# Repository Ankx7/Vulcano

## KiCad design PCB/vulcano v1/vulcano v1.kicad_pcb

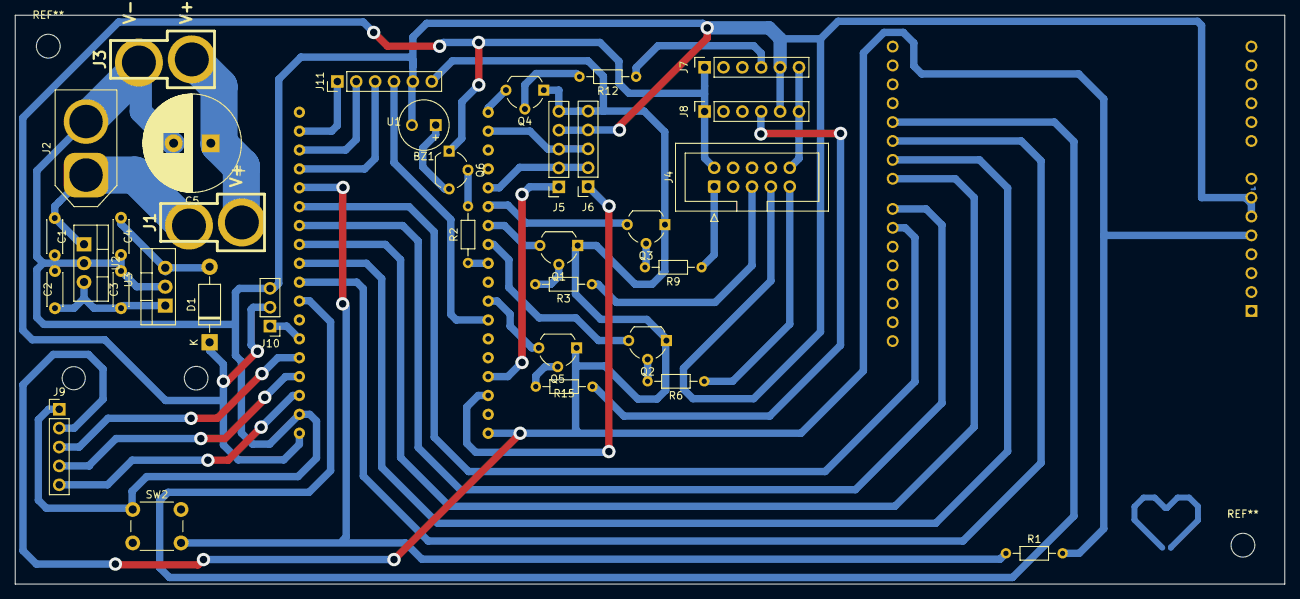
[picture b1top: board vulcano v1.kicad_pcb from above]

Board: 2 copper layers, 170.8 x 76.5 mm, 36 parts (1 on the bottom side), 45 nets.

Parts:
A1: Arduino_UNO_R2
BZ1: Buzzer; MagneticBuzzer_Kingstate_KCG0601
C1, C3: 0.33uF; C_Disc_D4.3mm_W1.9mm_P5.00mm
C2, C4: 0.1uF; C_Disc_D4.3mm_W1.9mm_P5.00mm
C5: C_Polarized_US; CP_Radial_D13.0mm_P5.00mm
D1: 1N4007; D_DO-41_SOD81_P10.16mm_Horizontal
J1, J3: Screw_Terminal_01x02; DEANS
J2: Screw_Terminal_01x02; AMASS_XT60-M_1x02_P7.20mm_Vertical
J4: Conn_02x05_Counter_Clockwise; IDC-Header_2x05_P2.54mm_Vertical
J5, J6: Conn_01x05_Pin; PinSocket_1x05_P2.54mm_Vertical
J7, J8: Conn_01x06_Pin; PinSocket_1x06_P2.54mm_Vertical
J9: Conn_01x05_Pin; PinHeader_1x05_P2.54mm_Vertical
J10: Conn_01x03_Pin; PinHeader_1x03_P2.54mm_Vertical
J11: Conn_01x06_Pin; PinHeader_1x06_P2.54mm_Vertical
Q1, Q2, Q3, Q4, Q5, Q6: BC547; TO-92_Wide
R1, R2, R3, R6, R9, R12, R15: 4k7; R_Axial_DIN0204_L3.6mm_D1.6mm_P7.62mm_Horizontal
SW2: SW_Push; SW_PUSH_6mm
U1: DOIT-ESP32-DEVKIT-V1; ESP32-DOIT-DEVKIT
U2: LM7809_TO220; TO-220-3_Vertical
U3: LM7806_TO220; TO-220-3_Vertical

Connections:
38KHZ: J4.10, J7.6, J8.6
+3.3V: A1.5 (+5V), J5.5, J6.5, J9.2, J11.6, Q1.1 (C), Q2.1 (C), Q3.1 (C), Q4.1 (C), Q5.1 (C), R1.2, U1.19 (3V3)
+5V: D1.1 (K), J4.2, J7.1, J8.1, J10.2, Q6.1 (C), U1.18 (VIN)
+6V: C4.1, D1.2 (A), U3.3 (VO)
+9V: C2.1, C3.1, U2.3 (VO), U3.1 (VI)
+12V: C1.1, J1.2, J2.1, U2.1 (VI)
AIN1: A1.22 (D7), U1.8 (GPIO25_ADC2-CH8_DAC1_RTC-GPIO6)
AIN2: A1.23 (D8), U1.7 (GPIO33_ADC1-CH5_RTC-GPIO8)
BIN1: A1.19 (D4), U1.11 (GPIO14_ADC2-CH6_HSPI-CLK_RTC-GPIO16)
BIN2: A1.24 (D9), U1.6 (GPIO32_ADC1-CH4_RTC-GPIO9)
CLK: J9.5, U1.16 (GPIO11_CSC/CMD)
CNY_1: J11.1, U1.2 (GPIO36_ADC-CH0_SENS-VP_RTC-GPIO0)
CNY_2: J11.2, U1.3 (GPIO39_ADC1-CH3_SENS-VN_RTC-GPIO3)
CNY_3: J11.3, U1.4 (GPIO34_ADC1-CH6_RTC-GPIO4)
CNY_4: J11.4, U1.25 (GPIO2_ADC2-CH2_RTC-GPIO12)
DI: J10.1, U1.13 (GPIO13_ADC2-CH4_HSPI-MOSI_RTC-GPIO14)
DT: J9.4, U1.15 (GPIO10_SWP/SD3)
GND: A1.6 (GND), A1.7 (GND), BZ1.2 (+), C1.2, C2.2, C3.2, C4.2, C5.2, J2.2, J3.2, J4.7, J5.4, J6.4, J7.5, J8.5, J9.1, J10.3, J11.5, SW2.1, U1.17 (GND), U2.2 (GND), U3.2 (GND)
INIT: R1.1, SW2.2, U1.5 (GPIO35_ADC1-CH7_RTC-GPIO5)
unnamed: BZ1.1 (-), Q6.3 (E)
unnamed: Q1.2 (B), R3.2
unnamed: Q2.2 (B), R6.2
unnamed: Q3.2 (B), R9.2
unnamed: Q4.2 (B), R12.2
unnamed: Q5.2 (B), R15.2
unnamed: Q6.2 (B), R2.2
PWMA: A1.20 (D5), U1.10 (GPIO27_ADC2-CH7_RTC-GPIO17)
PWMB: A1.21 (D6), U1.9 (GPIO26_ADC2-CH9_DAC2_RTC-GPIO7)
RX: J7.4, R12.1
RX_1: J8.4, R15.1
SCL: J5.3, J6.3, U1.35 (GPIO22_I2C-SCL)
SDA: J5.2, J6.2, U1.32 (GPIO21_I2C-SDA)
SENSOR_1_PIN: Q1.3 (E), U1.30 (GPIO18_VSPI-CLK)
SENSOR_2_PIN: Q2.3 (E), U1.29 (GPIO5_VSPI-CS0)
SENSOR_3_PIN: Q3.3 (E), U1.31 (GPIO19_VSPI-MISO)
SENSOR_4_PIN: Q4.3 (E), U1.36 (GPIO23_VSPI-MOSI)
SENSOR_5_PIN: Q5.3 (E), U1.26 (GPIO4_ADC2-CH0_RTC-GPIO10)
SW: J9.3, U1.14 (GPIO9_SHD/SD2)
Sensores: J4.5, R3.1
Sensores_2: J4.9, R6.1
Sensores_3: J4.1, R9.1
VCC: C5.1, J1.1, J3.1
X_SHUT_1: J6.1, U1.21 (GPIO7_SDO/SD0)
X_SHUT_2: J5.1, U1.22 (GPIO8_SDI/SD1)
buzzer: R2.1, U1.28 (GPIO17_UART2-TX)

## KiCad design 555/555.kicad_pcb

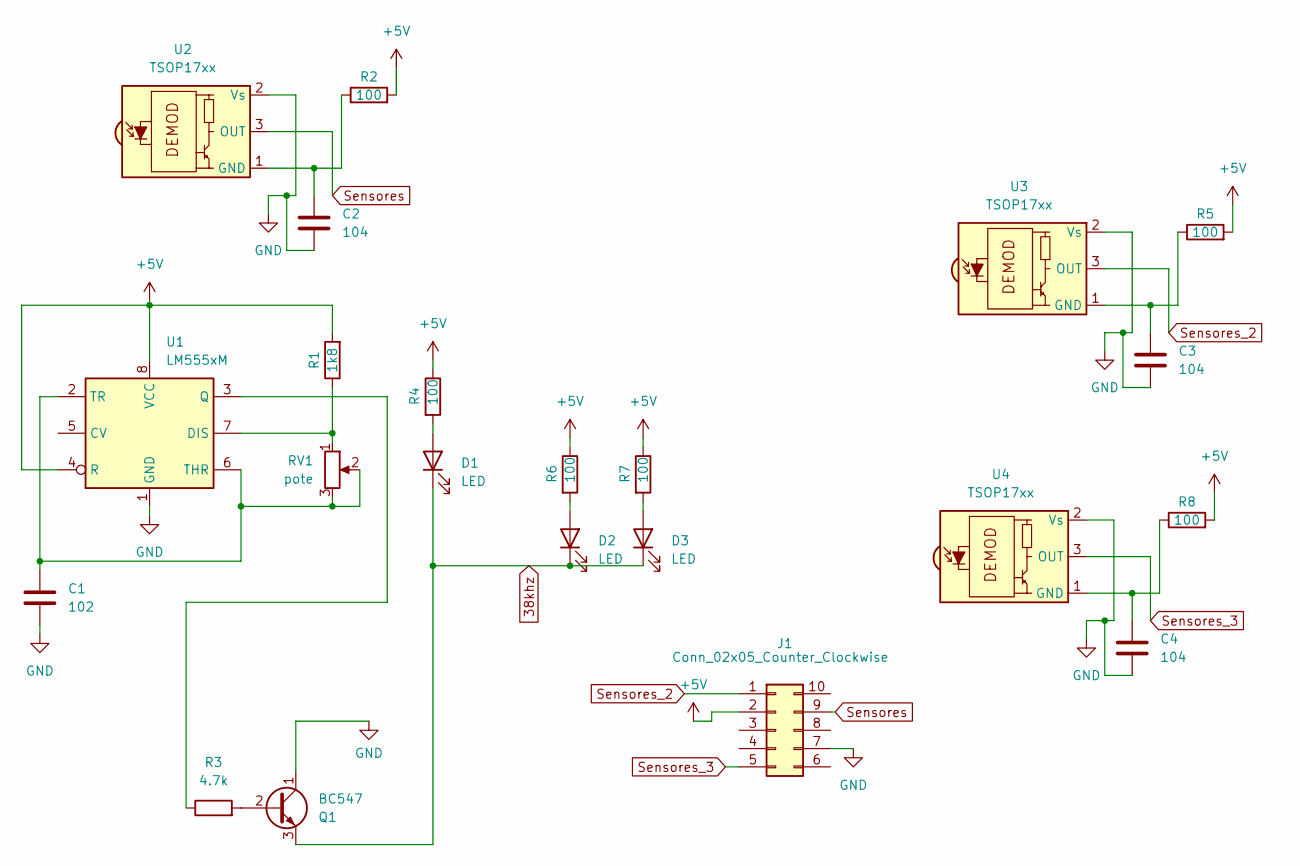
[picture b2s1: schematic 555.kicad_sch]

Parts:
C1: 102; C_Disc_D4.3mm_W1.9mm_P5.00mm
C2, C3, C4: 104; C_Disc_D4.3mm_W1.9mm_P5.00mm
D1, D2, D3: LED; LED_D5.0mm_Horizontal_O1.27mm_Z3.0mm
J1: Conn_02x05_Counter_Clockwise; IDC-Header_2x05_P2.54mm_Horizontal
Q1: BC547; TO-92_Wide
R1: 1k8; R_1206_3216Metric_Pad1.30x1.75mm_HandSolder
R2, R4, R5, R8: 100; R_1206_3216Metric_Pad1.30x1.75mm_HandSolder
R3: 4.7k; R_1206_3216Metric_Pad1.30x1.75mm_HandSolder
R6, R7: 100; R_Axial_DIN0207_L6.3mm_D2.5mm_P10.16mm_Horizontal
RV1: pote; Potentiometer_Bourns_3296W_Vertical
U1: LM555xM; DIP-8_W7.62mm
U2, U3, U4: TSOP17xx; TO-92S_Wide

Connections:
38khz: D1.1 (K), D2.1 (K), D3.1 (K), Q1.3 (E)
+5V: J1.2, R1.2, R2.2, R4.1, R5.2, R6.1, R7.1, R8.2, U1.4 (R), U1.8 (VCC)
GND: C1.2, C2.2, C3.2, C4.2, J1.7, Q1.1 (C), U1.1 (GND), U2.2 (Vs), U3.2 (Vs), U4.2 (Vs)
unnamed: D1.2 (A), R4.2
unnamed: D2.2 (A), R6.2
unnamed: D3.2 (A), R7.2
unnamed: Q1.2 (B), R3.2
unnamed: R1.1, RV1.1, U1.7 (DIS)
unnamed: R3.1, U1.3 (Q)
unnamed: C1.1, RV1.2, RV1.3, U1.2 (TR), U1.6 (THR)
unnamed: C2.1, R2.1, U2.1 (GND)
unnamed: C3.1, R5.1, U3.1 (GND)
unnamed: C4.1, R8.1, U4.1 (GND)
Sensores: J1.9, U2.3 (OUT)
Sensores_2: J1.1, U3.3 (OUT)
Sensores_3: J1.5, U4.3 (OUT)

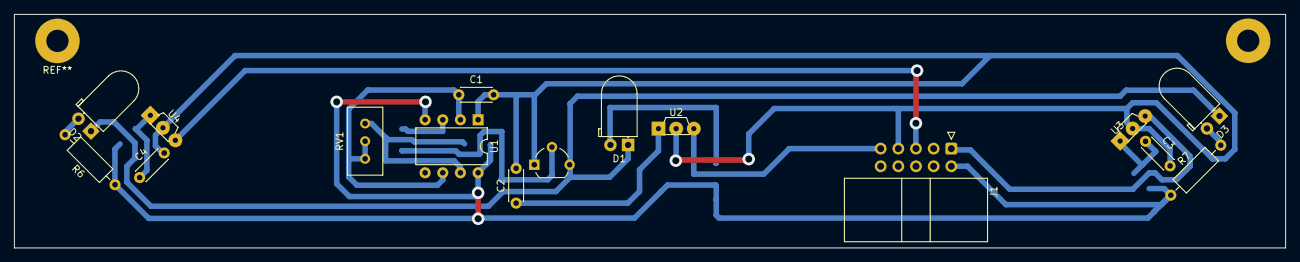
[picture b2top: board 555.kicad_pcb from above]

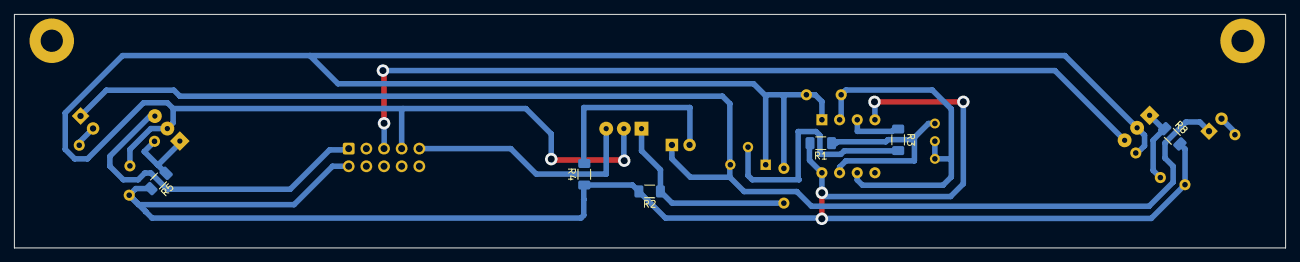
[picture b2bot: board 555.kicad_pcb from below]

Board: 2 copper layers, 182.8 x 33.6 mm, 22 parts (6 on the bottom side), 16 nets.

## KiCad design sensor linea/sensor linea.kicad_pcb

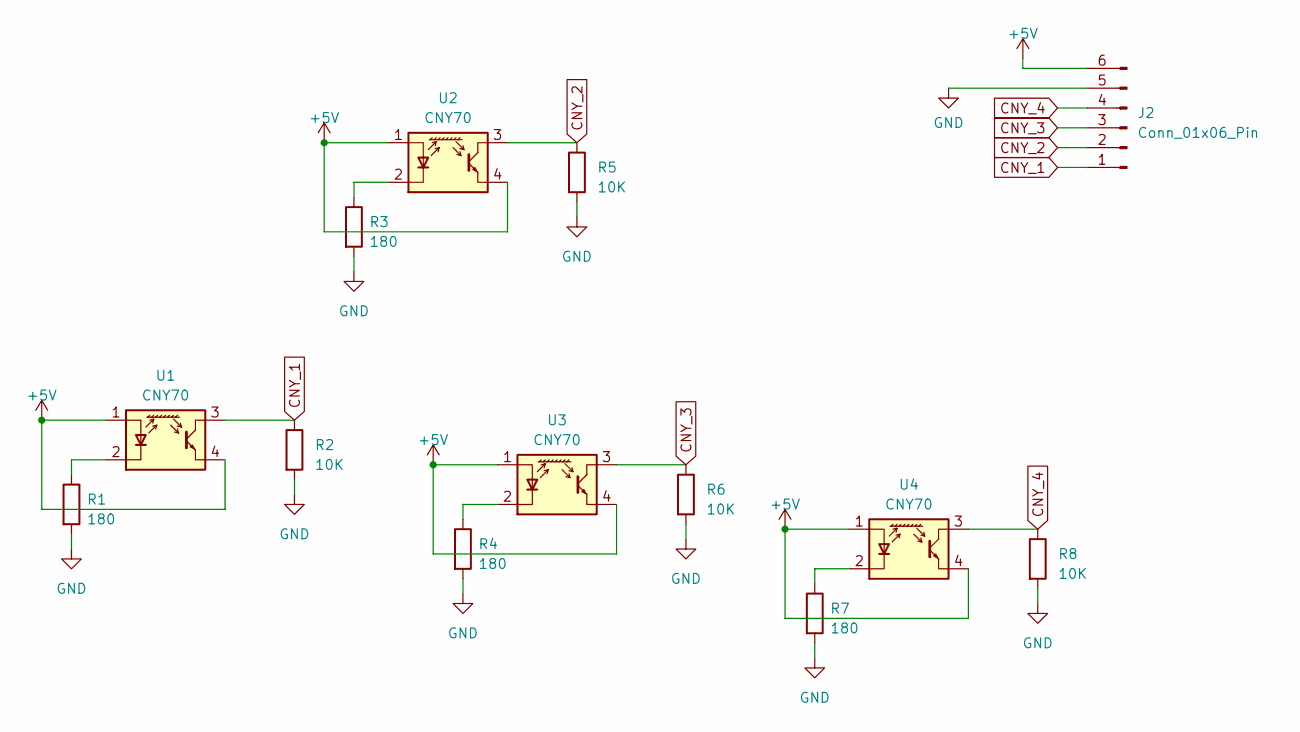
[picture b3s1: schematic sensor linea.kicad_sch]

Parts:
J2: Conn_01x06_Pin; PinHeader_1x06_P2.54mm_Horizontal
R1, R3, R4, R7: 180; R_1206_3216Metric_Pad1.30x1.75mm_HandSolder
R2, R5, R6, R8: 10K; R_1206_3216Metric_Pad1.30x1.75mm_HandSolder
U1, U2, U3, U4: CNY70; Vishay_CNY70

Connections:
+5V: J2.6, U1.1 (A), U1.4 (E), U2.1 (A), U2.4 (E), U3.1 (A), U3.4 (E), U4.1 (A), U4.4 (E)
CNY_1: J2.1, R2.1, U1.3 (C)
CNY_2: J2.2, R5.1, U2.3 (C)
CNY_3: J2.3, R6.1, U3.3 (C)
CNY_4: J2.4, R8.1, U4.3 (C)
GND: J2.5, R1.2, R2.2, R3.2, R4.2, R5.2, R6.2, R7.2, R8.2
unnamed: R1.1, U1.2 (K)
unnamed: R3.1, U2.2 (K)
unnamed: R4.1, U3.2 (K)
unnamed: R7.1, U4.2 (K)

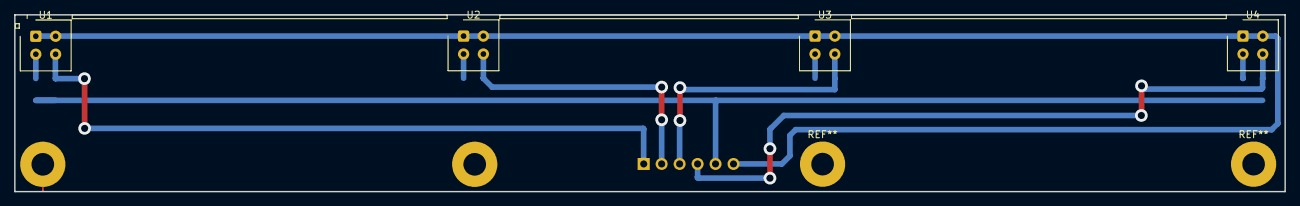
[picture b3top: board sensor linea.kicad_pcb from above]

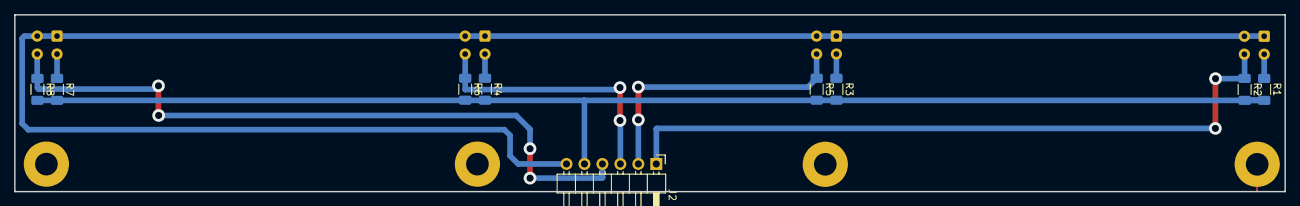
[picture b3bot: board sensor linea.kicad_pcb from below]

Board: 2 copper layers, 179.7 x 25.0 mm, 13 parts (9 on the bottom side), 10 nets.

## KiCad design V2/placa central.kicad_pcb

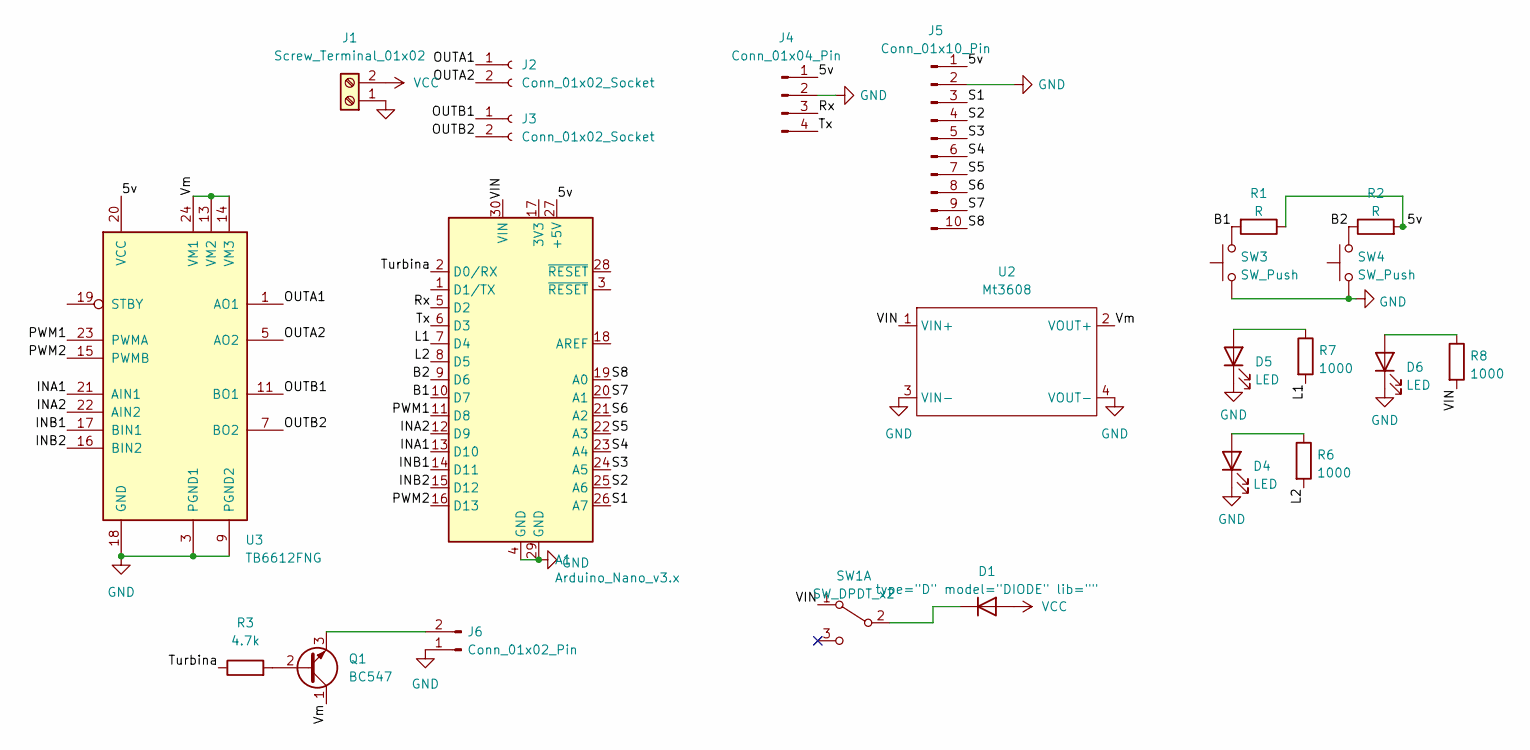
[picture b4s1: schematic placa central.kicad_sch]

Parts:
A1: Arduino_Nano_v3.x; Arduino_Nano
D1: type="D" model="DIODE" lib=""; D_5W_P5.08mm_Vertical_AnodeUp
D4, D5, D6: LED; LED_D3.0mm
J1: Screw_Terminal_01x02; PinSocket_1x02_P2.54mm_Vertical
J2, J3: Conn_01x02_Socket; PinSocket_1x02_P2.54mm_Vertical
J4: Conn_01x04_Pin; PinHeader_1x04_P2.54mm_Vertical
J5: Conn_01x10_Pin; PinHeader_1x10_P2.54mm_Vertical
J6: Conn_01x02_Pin; PinHeader_1x02_P2.54mm_Vertical
Q1: BC547; TO-92_Wide
R1, R2: R; R_1206_3216Metric_Pad1.30x1.75mm_HandSolder
R3: 4.7k; R_1206_3216Metric_Pad1.30x1.75mm_HandSolder
R6, R7, R8: 1000; R_1206_3216Metric_Pad1.30x1.75mm_HandSolder
SW1: SW_DPDT_x2; SW_Slide_1P2T_CK_OS102011MS2Q
SW3, SW4: SW_Push; SW_PUSH_6mm
U2: Mt3608; Sx1308
U3: TB6612FNG; SSOP-24_5.3x8.2mm_P0.65mm

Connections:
/5v: A1.27 (+5V), J4.1, J5.1, R1.1, R2.2, U3.20 (VCC)
/B1: A1.10 (D7), R1.2, SW3.2
/B2: A1.9 (D6), R2.1, SW4.2
/INA1: A1.13 (D10), U3.21 (AIN1)
/INA2: A1.12 (D9), U3.22 (AIN2)
/INB1: A1.14 (D11), U3.17 (BIN1)
/INB2: A1.15 (D12), U3.16 (BIN2)
/L1: A1.7 (D4), R7.2
/L2: A1.8 (D5), R6.2
/OUTA1: J2.1, U3.1 (AO1), U3.2 (AO1)
/OUTA2: J2.2, U3.5 (AO2), U3.6 (AO2)
/OUTB1: J3.1, U3.11 (BO1), U3.12 (BO1)
/OUTB2: J3.2, U3.7 (BO2), U3.8 (BO2)
/PWM1: A1.11 (D8), U3.23 (PWMA)
/PWM2: A1.16 (D13), U3.15 (PWMB)
/Rx: A1.5 (D2), J4.3
/S1: A1.26 (A7), J5.3
/S2: A1.25 (A6), J5.4
/S3: A1.24 (A5), J5.5
/S4: A1.23 (A4), J5.6
/S5: A1.22 (A3), J5.7
/S6: A1.21 (A2), J5.8
/S7: A1.20 (A1), J5.9
/S8: A1.19 (A0), J5.10
/Turbina: A1.2 (D0/RX), R3.1
/Tx: A1.6 (D3), J4.4
/VIN: A1.30 (VIN), R8.2, SW1.1 (A), U2.1 (VIN+)
/Vm: Q1.1 (C), U2.2 (VOUT+), U3.13 (VM2), U3.14 (VM3), U3.24 (VM1)
GND: A1.4 (GND), A1.29 (GND), D4.1 (K), D5.1 (K), D6.1 (K), J1.1, J4.2, J5.2, J6.1, SW3.1, SW4.1, U2.3 (VIN-), U2.4 (VOUT-), U3.3 (PGND1), U3.4 (PGND1), U3.9 (PGND2), U3.10 (PGND2), U3.18 (GND)
unnamed: D1.2 (K), SW1.2 (B)
unnamed: D4.2 (A), R6.1
unnamed: D5.2 (A), R7.1
unnamed: D6.2 (A), R8.1
unnamed: J6.2, Q1.3 (E)
unnamed: Q1.2 (B), R3.2
VCC: D1.1 (A), J1.2

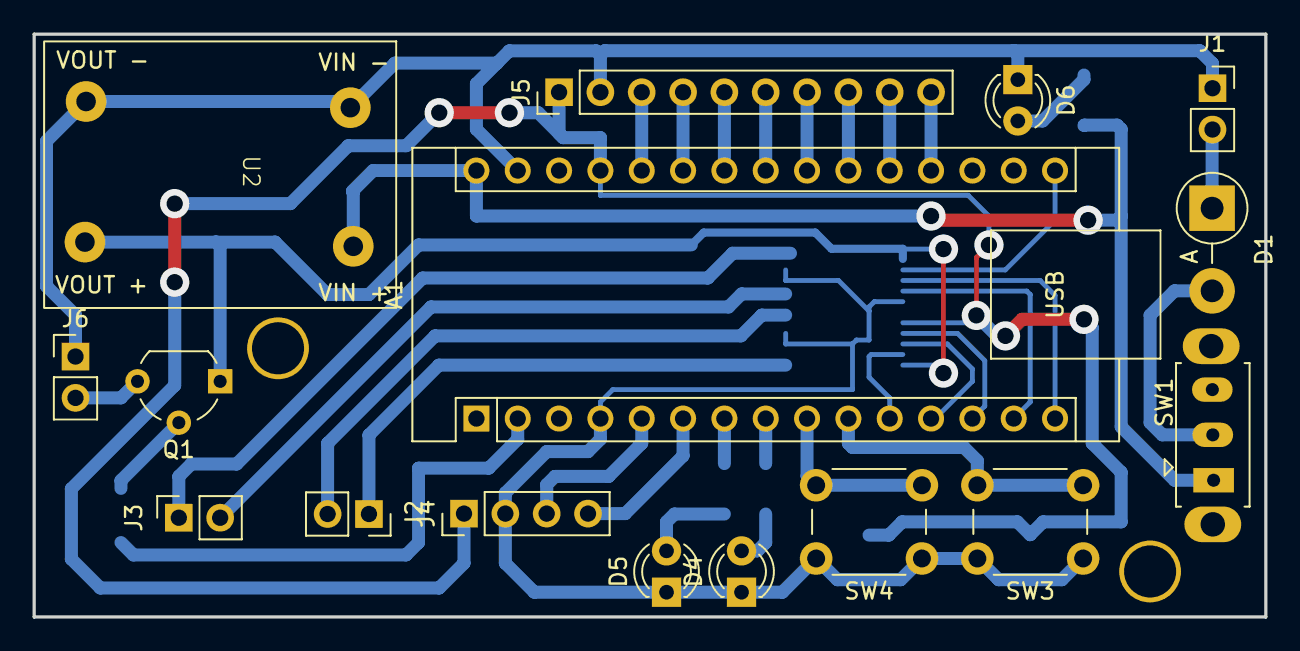
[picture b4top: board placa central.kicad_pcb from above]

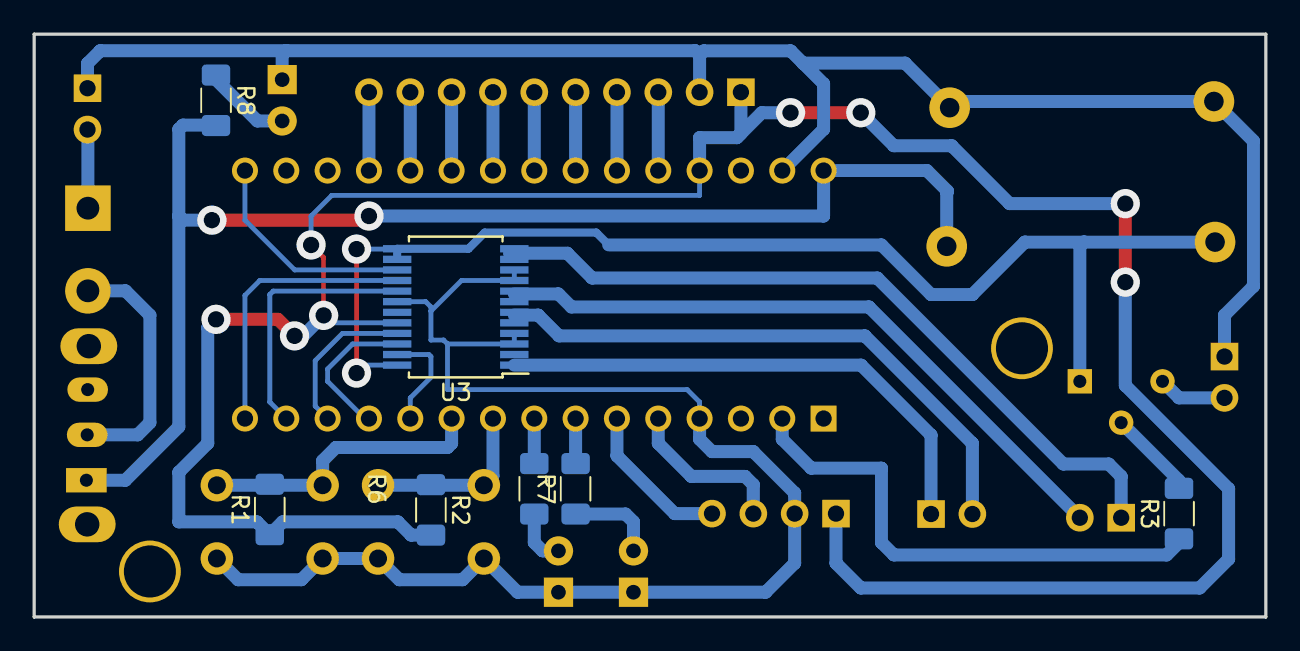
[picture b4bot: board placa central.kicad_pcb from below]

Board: 2 copper layers, 75.7 x 35.8 mm, 23 parts (7 on the bottom side), 36 nets.

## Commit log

2023-11-10 inico placa vulcano
2023-11-13 vl dual funcionando con esp
2023-11-21 remplazé la carpeta de códigos
2023-11-21 555 actualizada
2023-11-21 arranque PCB 555 falta rutear
2023-11-27 555 para imprimir
2023-12-08 sensor linea largo 5hz
2023-12-09 lalalalal
2023-12-09 pcb 555 centrada
2023-12-15 fusion
2023-12-15 falta revisar
2023-12-15 para imprimir
2024-01-02 imprimir
2024-01-24 soporte tof
2024-01-25 atmega
2024-01-26 pdf atemga
2024-01-29 placa principal
2024-02-24 pcb vulcano terminada (reviasala ana)
2024-02-25 placa central lista
2024-03-03 placa vulcano falta indicar tornillos
2024-03-03 Agujeros en pcb
